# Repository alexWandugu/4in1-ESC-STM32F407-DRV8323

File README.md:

# 4-in-1 Quadcopter ESC (STM32F407 + DRV8323RS)

**High-performance 4-in-1 Electronic Speed Controller** for BLDC motors in quadcopters/drones.

## Specifications
- **Battery**: 4S LiPo (5.2Ah 35C/60C)
- **Motor**: 1400KV BLDC, ~7A max efficient current per motor
- **MOSFET**: MCG4D8N04YHE3-TP (x12 for 4-in-1)
- **Gate Driver**: DRV8323RS (x4)
- **MCU**: STM32F407VET6
- **Layout**: 4-in-1 ESC board
- **Firmware**: Custom (in development) — supports [target protocol, e.g., DShot, PWM]

## Features
- 4 independent 3-phase half-bridges
- High-current power stage optimized for 4S
- SPI / UART interface for configuration and telemetry
- Current sensing & protection

## Project Status
- Schematic V2 complete (multi-motor sheets)
- PCB layout in progress (see attached files)
- Firmware skeleton in development

## Repository Contents
- `project files (kicad)/` — KiCad 8+ schematic + PCB files
- `docs/` — Schematics PDF, BOM, images

## Quick Start
1. Clone repo
2. Open `hardware/ESC_4in1.kicad_pro` in KiCad
3. Review power stage, gate driver, and MCU sections
4. Generate Gerbers for manufacturing

## Firmware
(Instructions coming soon — STM32CubeIDE / PlatformIO)

## Contributing
Contributions welcome! See [CONTRIBUTING.md](CONTRIBUTING.md) (create later).

## License
MIT License — see [LICENSE](LICENSE) file.

---

## Roadmap & Future Improvements

### High Priority
- **Board Miniaturization**
  - Current dimensions: **108.6 × 77.5 mm** (4 layers)
  - Target: Reduce to **≤ 70 × 70 mm** or closer to standard 30.5×30.5mm / 40×40mm mounting patterns while maintaining proper thermal performance and clearance.
  - Optimize component placement and routing
  - Evaluate moving to 6-layer PCB if it enables significant size reduction
  - Improve power plane design and thermal vias under MOSFETs

- **Firmware Development**
  - Implement full BLDC FOC / Trapezoidal control using STM32F407
  - Support DShot600 / DShot1200 protocols
  - Current sensing and over-current protection
  - Telemetry (voltage, current, temperature, RPM)
  - DRV8323RS configuration via SPI
  - Sensorless startup and BEMF detection tuning
  - PID tuning for smooth throttle response

### Medium Priority
- Add onboard 5V / 3.3V BEC with better filtering
- Improve EMI/EMC performance (snubbers, capacitor placement)
- Add status LEDs and debugging interfaces (SWD + UART)
- Thermal simulation and real-world heat testing
- Input protection (TVS diodes, reverse polarity)
- Create a configurable GUI tool (Python / Qt) for tuning parameters

### Long Term
- Support higher current motors (optimize MOSFET cooling)
- 6S battery compatibility
- Open-source configurator tool
- Flight testing on a test quadcopter
- Documentation for assembly and calibration

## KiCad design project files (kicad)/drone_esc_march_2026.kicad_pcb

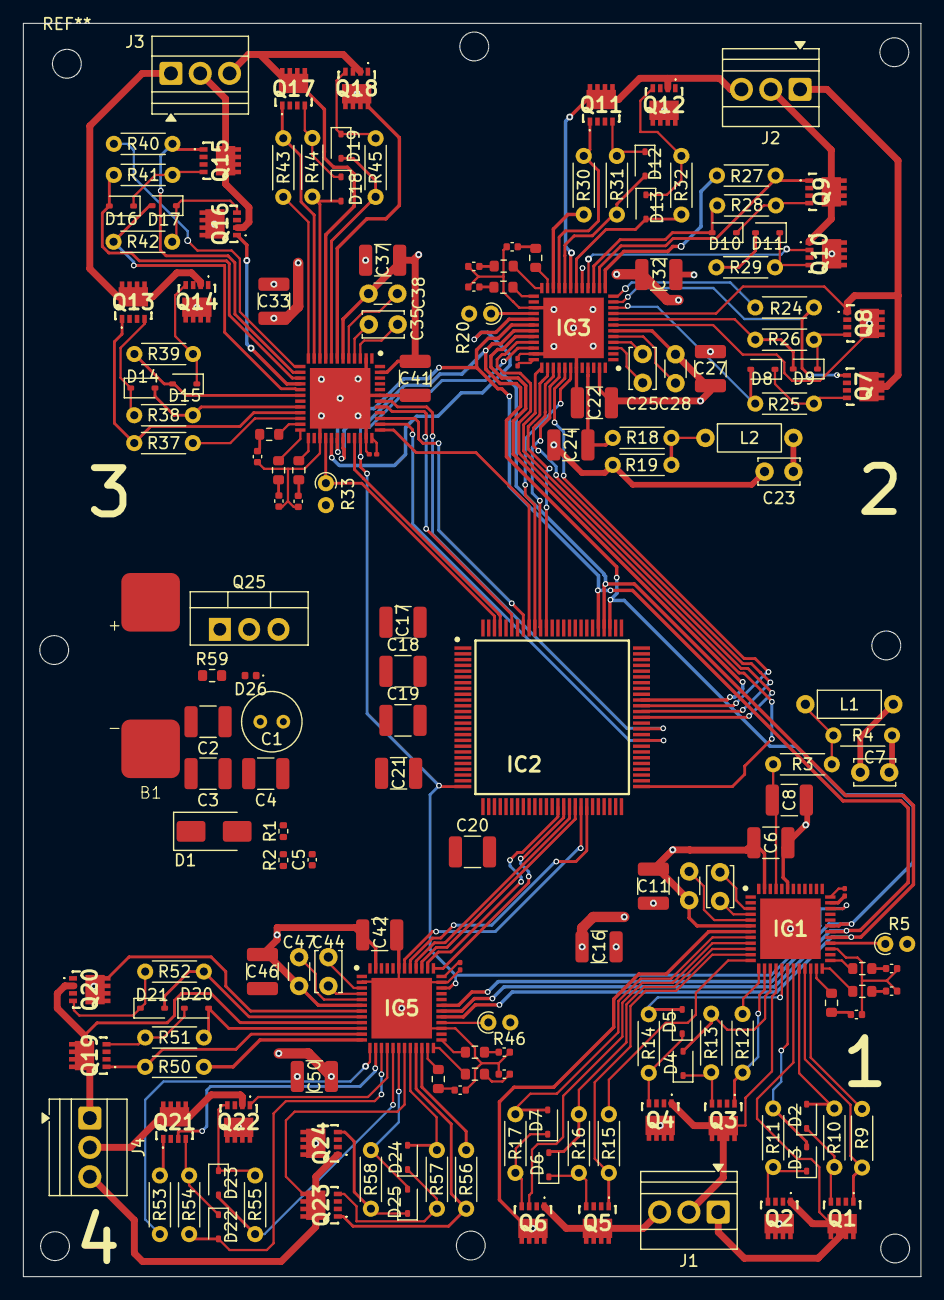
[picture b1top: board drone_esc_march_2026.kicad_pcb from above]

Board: 4 copper layers, 77.8 x 108.6 mm, 172 parts (0 on the bottom side), 162 nets.

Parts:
B1: Battery-Solder-Pads
C1: 1000u; C_Radial_D5.0mm_H7.0mm_P2.00mm
C2, C3, C4, C6, C22, C33, C42: 47u 25V; C_1210_3225Metric
C5, C13, C14, C15, C29, C30, C31, C36, C39, C40, C45, C48, C49: 100n; C_0402_1005Metric
C7, C23: 47u; C_Disc_D3.4mm_W2.1mm_P2.50mm
C8, C24: 22u 10V; C_1210_3225Metric
C9, C25, C35, C44: 100n 25V; C_Disc_D3.4mm_W2.1mm_P2.50mm
C10, C26, C34, C43: 0.1u; C_0201_0603Metric
C11, C27, C37, C46: 47u; C_1210_3225Metric
C12, C28, C38, C47: 2.2u; C_Disc_D3.0mm_W1.6mm_P2.50mm
C16, C32, C41, C50: 10u 25V; C_1210_3225Metric
C17, C18, C19, C20: 0.1u 10V; C_1210_3225Metric
C21: 4.7u 10V; C_1210_3225Metric
D1: SMAJ20CA; D_SMA
D2, D3, D4, D5, D6, D7, D8, D9, D10, D11, D12, D13, D14, D15, D16, D17, D18, D19, D20, D21, D22, D23, D24, D25: 1N4148WS; D_SOD-323
D26: D_Zener; D_0402_1005Metric
IC1, IC3, IC4, IC5: DRV8323RSRGZT; QFN50P700X700X100-49N-D
IC2: STM32F407VET6; QFP50P1600X1600X160-100N
J1, J2, J3, J4: Screw_Terminal_01x03; TerminalBlock_Xinya_XY308-2.54-3P_1x03_P2.54mm_Horizontal
L1, L2: 10u 1A; L_Axial_L5.3mm_D2.2mm_P7.62mm_Horizontal_Vishay_IM-1
Q1, Q2, Q3, Q4, Q5, Q6, Q7, Q8, Q9, Q10, Q11, Q12, Q13, Q14, Q15, Q16, Q17, Q18, Q19, Q20, Q21, Q22, Q23, Q24: MCG4D8N04YHE3-TP; MCG20N06HE3TP
Q25: IRF4905; TO-220-3_Vertical
R1: 10K; R_0402_1005Metric
R2: 1K; R_0402_1005Metric
R3, R18: 10K; R_Axial_DIN0204_L3.6mm_D1.6mm_P5.08mm_Horizontal
R4, R19: 3.3K; R_Axial_DIN0204_L3.6mm_D1.6mm_P5.08mm_Horizontal
R5, R20, R33, R46: 10K; R_Axial_DIN0204_L3.6mm_D1.6mm_P1.90mm_Vertical
R6, R7, R8, R21, R22, R23, R34, R35, R36, R47, R48, R49: 1K; R_0603_1608Metric
R9, R12, R15, R24, R27, R30, R37, R40, R43, R50, R53, R56: 5m; R_Axial_DIN0204_L3.6mm_D1.6mm_P5.08mm_Horizontal
R10, R11, R13, R14, R16, R17, R25, R26, R28, R29, R31, R32, R38, R39, R41, R42, R44, R45, R51, R52, R54, R55, R57, R58: 22; R_Axial_DIN0204_L3.6mm_D1.6mm_P5.08mm_Horizontal
R59: 10k; R_0603_1608Metric

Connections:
+3.3V: C7.1, C17.2, C18.2, C19.2, C20.2, C21.2, C23.1, IC2.11 (VDD_1), IC2.19 (VDD_2), IC2.22 (VDDA), IC2.28 (VDD_3), IC2.50 (VDD_4), IC2.75 (VDD_5), IC2.100 (VDD_6), L1.2, L2.2, R5.2, R20.2, R33.2, R46.2
+Vbat: C1.1, C2.1, C3.1, C4.1, C6.1, C11.2, C12.2, C16.1, C22.1, C27.2, C28.2, C32.1, C33.1, C37.2, C38.2, C41.1, C42.1, C46.2, C47.2, C50.1, D1.2 (A2), D26.1 (K), IC1.6 (VM), IC1.7 (VDRAIN), IC1.47 (VIN), IC3.6 (VM), IC3.7 (VDRAIN), IC3.47 (VIN), IC4.6 (VM), IC4.7 (VDRAIN), IC4.47 (VIN), IC5.6 (VM), IC5.7 (VDRAIN), IC5.47 (VIN), Q2.5 (D_1), Q2.6 (D_2), Q2.7 (D_3), Q2.8 (D_4), Q2.9 (D_5), Q4.5 (D_1), Q4.6 (D_2), Q4.7 (D_3), Q4.8 (D_4), Q4.9 (D_5), Q6.5 (D_1), Q6.6 (D_2), Q6.7 (D_3), Q6.8 (D_4), Q6.9 (D_5), Q8.5 (D_1), Q8.6 (D_2), Q8.7 (D_3), Q8.8 (D_4), Q8.9 (D_5), Q10.5 (D_1), Q10.6 (D_2), Q10.7 (D_3), Q10.8 (D_4), Q10.9 (D_5), Q12.5 (D_1), Q12.6 (D_2), Q12.7 (D_3), Q12.8 (D_4), Q12.9 (D_5), Q14.5 (D_1), Q14.6 (D_2), Q14.7 (D_3), Q14.8 (D_4), Q14.9 (D_5), Q16.5 (D_1), Q16.6 (D_2), Q16.7 (D_3), Q16.8 (D_4), Q16.9 (D_5), Q18.5 (D_1), Q18.6 (D_2), Q18.7 (D_3), Q18.8 (D_4), Q18.9 (D_5), Q20.5 (D_1), Q20.6 (D_2), Q20.7 (D_3), Q20.8 (D_4), Q20.9 (D_5), Q22.5 (D_1), Q22.6 (D_2), Q22.7 (D_3), Q22.8 (D_4), Q22.9 (D_5), Q24.5 (D_1), Q24.6 (D_2), Q24.7 (D_3), Q24.8 (D_4), Q24.9 (D_5), Q25.3 (S), R1.2
/GATE_DRIVER M2/CPH2: C25.2, IC3.4 (CPH)
/GATE_DRIVER M2/CPL2: C25.1, IC3.3 (CPL)
/GATE_DRIVER M2/DVDD2: C26.1, IC3.36 (DVDD)
/GATE_DRIVER M2/SOA2: IC3.25 (SOA), R21.1
/GATE_DRIVER M2/SOB2: IC3.24 (SOB), R22.1
/GATE_DRIVER M2/SOC2: IC3.23 (SOC), R23.1
/GATE_DRIVER M2/SW2: C24.2, IC3.45 (SW), R18.1
/GATE_DRIVER M2/VCP2: C28.1, IC3.5 (VCP)
/GATE_DRIVER M3/CPH3: C35.2, IC4.4 (CPH)
/GATE_DRIVER M3/CPL3: C35.1, IC4.3 (CPL)
/GATE_DRIVER M3/DVDD3: C34.1, IC4.36 (DVDD)
/GATE_DRIVER M3/SOA3: IC4.25 (SOA), R34.1
/GATE_DRIVER M3/SOB3: IC4.24 (SOB), R35.1
/GATE_DRIVER M3/SOC3: IC4.23 (SOC), R36.1
/GATE_DRIVER M3/VCP3: C38.1, IC4.5 (VCP)
/GATE_DRIVER M4/CPH4: C44.2, IC5.4 (CPH)
/GATE_DRIVER M4/CPL4: C44.1, IC5.3 (CPL)
/GATE_DRIVER M4/DVDD4: C43.1, IC5.36 (DVDD)
/GATE_DRIVER M4/SOA4: IC5.25 (SOA), R47.1
/GATE_DRIVER M4/SOB4: IC5.24 (SOB), R48.1
/GATE_DRIVER M4/SOC4: IC5.23 (SOC), R49.1
/GATE_DRIVER M4/VCP4: C47.1, IC5.5 (VCP)
/GATE_DRIVER_MAIN/CPH1: C9.2, IC1.4 (CPH)
/GATE_DRIVER_MAIN/CPL1: C9.1, IC1.3 (CPL)
/GATE_DRIVER_MAIN/DVDD1: C10.1, IC1.36 (DVDD)
/GATE_DRIVER_MAIN/SOA1: IC1.25 (SOA), R6.1
/GATE_DRIVER_MAIN/SOB1: IC1.24 (SOB), R7.1
/GATE_DRIVER_MAIN/SOC1: IC1.23 (SOC), R8.1
/GATE_DRIVER_MAIN/SW1: C8.2, IC1.45 (SW), R3.1
/GATE_DRIVER_MAIN/VCP1: C12.1, IC1.5 (VCP)
/POWER_BRIDGE M1/GHA1: D3.1 (K), Q2.4 (G), R11.2
/POWER_BRIDGE M1/GHB1: D5.1 (K), Q4.4 (G), R14.2
/POWER_BRIDGE M1/GHC1: D7.1 (K), Q6.4 (G), R17.2
/POWER_BRIDGE M1/GLA1: D2.1 (K), Q1.4 (G), R10.2
/POWER_BRIDGE M1/GLB1: D4.1 (K), Q3.4 (G), R13.2
/POWER_BRIDGE M1/GLC1: D6.1 (K), Q5.4 (G), R16.2
/POWER_BRIDGE M2/GHA2: D9.1 (K), Q8.4 (G), R26.2
/POWER_BRIDGE M2/GHB2: D11.1 (K), Q10.4 (G), R29.2
/POWER_BRIDGE M2/GHC2: D13.1 (K), Q12.4 (G), R32.2
/POWER_BRIDGE M2/GLA2: D8.1 (K), Q7.4 (G), R25.2
/POWER_BRIDGE M2/GLB2: D10.1 (K), Q9.4 (G), R28.2
/POWER_BRIDGE M2/GLC2: D12.1 (K), Q11.4 (G), R31.2
/POWER_BRIDGE M3/GHA3: D15.1 (K), Q14.4 (G), R39.2
/POWER_BRIDGE M3/GHB3: D17.1 (K), Q16.4 (G), R42.2
/POWER_BRIDGE M3/GHC3: D19.1 (K), Q18.4 (G), R45.2
/POWER_BRIDGE M3/GLA3: D14.1 (K), Q13.4 (G), R38.2
/POWER_BRIDGE M3/GLB3: D16.1 (K), Q15.4 (G), R41.2
/POWER_BRIDGE M3/GLC3: D18.1 (K), Q17.4 (G), R44.2
/POWER_BRIDGE M4/GHA4: D21.1 (K), Q20.4 (G), R52.2
/POWER_BRIDGE M4/GHB4: D23.1 (K), Q22.4 (G), R55.2
/POWER_BRIDGE M4/GHC4: D25.1 (K), Q24.4 (G), R58.2
/POWER_BRIDGE M4/GLA4: D20.1 (K), Q19.4 (G), R51.2
/POWER_BRIDGE M4/GLB4: D22.1 (K), Q21.4 (G), R54.2
/POWER_BRIDGE M4/GLC4: D24.1 (K), Q23.4 (G), R57.2
ADC123_A_M1: C13.2, IC2.15 (PC0), R6.2
ADC123_A_M2: C29.2, IC2.29 (PA4), R21.2
ADC123_A_M3: C36.2, IC2.33 (PC4), R34.2
ADC123_A_M4: C45.2, IC2.36 (PB1), R47.2
ADC123_B_M1: C14.2, IC2.16 (PC1), R7.2
ADC123_B_M2: C30.2, IC2.30 (PA5), R22.2
ADC123_B_M3: C39.2, IC2.34 (PC5), R35.2
ADC123_B_M4: C48.2, IC2.32 (PA7), R48.2
ADC123_C_M1: C15.2, IC2.17 (PC2), R8.2
ADC123_C_M2: C31.2, IC2.31 (PA6), R23.2
ADC123_C_M3: C40.2, IC2.35 (PB0), R36.2
ADC123_C_M4: C49.2, IC2.26 (PA3), R49.2
AMP_CALLIB: IC1.34 (CAL), IC2.25 (PA2), IC3.34 (CAL), IC4.34 (CAL), IC5.34 (CAL)
EN_DRIVER_M1: IC1.33 (ENABLE), IC2.24 (PA1)
EN_DRIVER_M2: IC2.51 (PB12), IC3.33 (ENABLE)
EN_DRIVER_M3: IC2.97 (PE0), IC4.33 (ENABLE)
EN_DRIVER_M4: IC2.2 (PE3), IC5.33 (ENABLE)
Fault_M1: IC1.28 (NFAULT), IC2.23 (PA0), R5.1
Fault_M2: IC2.37 (PB2), IC3.28 (NFAULT), R20.1
Fault_M3: IC2.98 (PE1), IC4.28 (NFAULT), R33.1
Fault_M4: IC2.3 (PE4), IC5.28 (NFAULT), R46.1
GHA_M1: D3.2 (A), IC1.18 (GHC), R11.1
GHA_M2: D9.2 (A), IC3.8 (GHA), R26.1
GHA_M3: D15.2 (A), IC4.18 (GHC), R39.1
GHA_M4: D21.2 (A), IC5.8 (GHA), R52.1
GHB_M1: D5.2 (A), IC1.17 (GHB), R14.1
GHB_M2: D11.2 (A), IC3.17 (GHB), R29.1
GHB_M3: D17.2 (A), IC4.17 (GHB), R42.1
GHB_M4: D23.2 (A), IC5.17 (GHB), R55.1
GHC_M1: D7.2 (A), IC1.8 (GHA), R17.1
GHC_M2: D13.2 (A), IC3.18 (GHC), R32.1
GHC_M3: D19.2 (A), IC4.8 (GHA), R45.1
GHC_M4: D25.2 (A), IC5.18 (GHC), R58.1
GLA_M1: D2.2 (A), IC1.20 (GLC), R10.1
GLA_M2: D8.2 (A), IC3.10 (GLA), R25.1
GLA_M3: D14.2 (A), IC4.20 (GLC), R38.1
GLA_M4: D20.2 (A), IC5.10 (GLA), R51.1
GLB_M1: D4.2 (A), IC1.15 (GLB), R13.1
GLB_M2: D10.2 (A), IC3.15 (GLB), R28.1
GLB_M3: D16.2 (A), IC4.15 (GLB), R41.1
GLB_M4: D22.2 (A), IC5.15 (GLB), R54.1
GLC_M1: D6.2 (A), IC1.10 (GLA), R16.1
GLC_M2: D12.2 (A), IC3.20 (GLC), R31.1
GLC_M3: D18.2 (A), IC4.10 (GLA), R44.1
GLC_M4: D24.2 (A), IC5.20 (GLC), R57.1
GND: B1.2 (-), C1.2, C2.2, C3.2, C4.2, C5.1, C6.2, C7.2, C8.1, C10.2, C11.1, C13.1, C14.1, C15.1, C16.2, C17.1, C18.1, C19.1, C20.1, C21.1, C22.2, C23.2, C24.1, C26.2, C27.1, C29.1, C30.1, C31.1, C32.2, C33.2, C34.2, C36.1, C37.1, C39.1, C40.1, C41.2, C42.2, C43.2, C45.1, C46.1, C48.1, C49.1, C50.2, D1.1 (A1), IC1.2 (PGND), IC1.12 (SNA), IC1.13 (SNB), IC1.22 (SNC), IC1.27 (DGND), IC1.35 (AGND), IC1.43 (BGND), IC1.49 (THERMAL_PAD), IC2.10 (VSS_1), IC2.20 (VSSA), IC2.27 (VSS_2), IC2.74 (VSS_3), IC2.99 (VSS_4), IC3.2 (PGND), IC3.12 (SNA), IC3.13 (SNB), IC3.22 (SNC), IC3.27 (DGND), IC3.35 (AGND), IC3.43 (BGND), IC3.49 (THERMAL_PAD), IC4.2 (PGND), IC4.12 (SNA), IC4.13 (SNB), IC4.22 (SNC), IC4.27 (DGND), IC4.35 (AGND), IC4.43 (BGND), IC4.49 (THERMAL_PAD), IC5.2 (PGND), IC5.12 (SNA), IC5.13 (SNB), IC5.22 (SNC), IC5.27 (DGND), IC5.35 (AGND), IC5.43 (BGND), IC5.49 (THERMAL_PAD), R2.1, R4.1, R9.1, R12.1, R15.1, R19.1, R24.1, R27.1, R30.1, R37.1, R40.1, R43.1, R50.1, R53.1, R56.1, R59.1
LSA ShuntAmp_M1+: IC1.21 (SPC), Q1.1 (S_1), Q1.2 (S_2), Q1.3 (S_3), R9.2
LSA ShuntAmp_M2+: IC3.11 (SPA), Q7.1 (S_1), Q7.2 (S_2), Q7.3 (S_3), R24.2
LSA ShuntAmp_M3+: IC4.21 (SPC), Q13.1 (S_1), Q13.2 (S_2), Q13.3 (S_3), R37.2
LSA ShuntAmp_M4+: IC5.11 (SPA), Q19.1 (S_1), Q19.2 (S_2), Q19.3 (S_3), R50.2
LSB ShuntAmp_M1+: IC1.14 (SPB), Q3.1 (S_1), Q3.2 (S_2), Q3.3 (S_3), R12.2
LSB ShuntAmp_M2+: IC3.14 (SPB), Q9.1 (S_1), Q9.2 (S_2), Q9.3 (S_3), R27.2
LSB ShuntAmp_M3+: IC4.14 (SPB), Q15.1 (S_1), Q15.2 (S_2), Q15.3 (S_3), R40.2
LSB ShuntAmp_M4+: IC5.14 (SPB), Q21.1 (S_1), Q21.2 (S_2), Q21.3 (S_3), R53.2
LSC ShuntAmp_M1+: IC1.11 (SPA), Q5.1 (S_1), Q5.2 (S_2), Q5.3 (S_3), R15.2
LSC ShuntAmp_M2+: IC3.21 (SPC), Q11.1 (S_1), Q11.2 (S_2), Q11.3 (S_3), R30.2
LSC ShuntAmp_M3+: IC4.11 (SPA), Q17.1 (S_1), Q17.2 (S_2), Q17.3 (S_3), R43.2
LSC ShuntAmp_M4+: IC5.21 (SPC), Q23.1 (S_1), Q23.2 (S_2), Q23.3 (S_3), R56.2
unnamed: B1.1 (+), Q25.2 (D)
unnamed: D26.2 (A), Q25.1 (G), R59.2
unnamed: L1.1, R3.2, R4.2
unnamed: L2.1, R18.2, R19.2
PHASE A - M1: IC1.19 (SHC), J1.1, Q1.5 (D_1), Q1.6 (D_2), Q1.7 (D_3), Q1.8 (D_4), Q1.9 (D_5), Q2.1 (S_1), Q2.2 (S_2), Q2.3 (S_3)
PHASE A - M2: IC3.9 (SHA), J2.1, Q7.5 (D_1), Q7.6 (D_2), Q7.7 (D_3), Q7.8 (D_4), Q7.9 (D_5), Q8.1 (S_1), Q8.2 (S_2), Q8.3 (S_3)
PHASE A - M3: IC4.19 (SHC), J3.1, Q13.5 (D_1), Q13.6 (D_2), Q13.7 (D_3), Q13.8 (D_4), Q13.9 (D_5), Q14.1 (S_1), Q14.2 (S_2), Q14.3 (S_3)
PHASE A - M4: IC5.9 (SHA), J4.1, Q19.5 (D_1), Q19.6 (D_2), Q19.7 (D_3), Q19.8 (D_4), Q19.9 (D_5), Q20.1 (S_1), Q20.2 (S_2), Q20.3 (S_3)
PHASE B - M1: IC1.16 (SHB), J1.2, Q3.5 (D_1), Q3.6 (D_2), Q3.7 (D_3), Q3.8 (D_4), Q3.9 (D_5), Q4.1 (S_1), Q4.2 (S_2), Q4.3 (S_3)
PHASE B - M2: IC3.16 (SHB), J2.2, Q9.5 (D_1), Q9.6 (D_2), Q9.7 (D_3), Q9.8 (D_4), Q9.9 (D_5), Q10.1 (S_1), Q10.2 (S_2), Q10.3 (S_3)
PHASE B - M3: IC4.16 (SHB), J3.2, Q15.5 (D_1), Q15.6 (D_2), Q15.7 (D_3), Q15.8 (D_4), Q15.9 (D_5), Q16.1 (S_1), Q16.2 (S_2), Q16.3 (S_3)
PHASE B - M4: IC5.16 (SHB), J4.2, Q21.5 (D_1), Q21.6 (D_2), Q21.7 (D_3), Q21.8 (D_4), Q21.9 (D_5), Q22.1 (S_1), Q22.2 (S_2), Q22.3 (S_3)
PHASE C - M1: IC1.9 (SHA), J1.3, Q5.5 (D_1), Q5.6 (D_2), Q5.7 (D_3), Q5.8 (D_4), Q5.9 (D_5), Q6.1 (S_1), Q6.2 (S_2), Q6.3 (S_3)
PHASE C - M2: IC3.19 (SHC), J2.3, Q11.5 (D_1), Q11.6 (D_2), Q11.7 (D_3), Q11.8 (D_4), Q11.9 (D_5), Q12.1 (S_1), Q12.2 (S_2), Q12.3 (S_3)
PHASE C - M3: IC4.9 (SHA), J3.3, Q17.5 (D_1), Q17.6 (D_2), Q17.7 (D_3), Q17.8 (D_4), Q17.9 (D_5), Q18.1 (S_1), Q18.2 (S_2), Q18.3 (S_3)
PHASE C - M4: IC5.19 (SHC), J4.3, Q23.5 (D_1), Q23.6 (D_2), Q23.7 (D_3), Q23.8 (D_4), Q23.9 (D_5), Q24.1 (S_1), Q24.2 (S_2), Q24.3 (S_3)
SPI1_MISO: IC1.29 (SDO), IC2.79 (PC11), IC3.29 (SDO), IC4.29 (SDO), IC5.29 (SDO)
SPI1_MOSI: IC1.30 (SDI), IC2.80 (PC12), IC3.30 (SDI), IC4.30 (SDI), IC5.30 (SDI)
SPI1_NSS_M1: IC1.32 (NSCS), IC2.83 (PD2)
SPI1_NSS_M2: IC2.66 (PC9), IC3.32 (NSCS)
SPI1_NSS_M3: IC2.62 (PD15), IC4.32 (NSCS)
SPI1_NSS_M4: IC2.1 (PE2), IC5.32 (NSCS)
SPI1_SCK: IC1.31 (SCLK), IC2.78 (PC10), IC3.31 (SCLK), IC4.31 (SCLK), IC5.31 (SCLK)
VbatSense: C5.2, IC2.18 (PC3), R1.1, R2.2
hsideA_M1: IC1.37 (INHA), IC2.67 (PA8)
hsideA_M2: IC2.63 (PC6), IC3.37 (INHA)
hsideA_M3: IC2.92 (PB6), IC4.37 (INHA)
hsideA_M4: IC2.40 (PE9), IC5.37 (INHA)
hsideB_M1: IC1.39 (INHB), IC2.68 (PA9)
hsideB_M2: IC2.64 (PC7), IC3.39 (INHB)
hsideB_M3: IC2.93 (PB7), IC4.39 (INHB)
hsideB_M4: IC2.42 (PE11), IC5.39 (INHB)
hsideC_M1: IC1.41 (INHC), IC2.69 (PA10)
hsideC_M2: IC2.65 (PC8), IC3.41 (INHC)
hsideC_M3: IC2.95 (PB8), IC4.41 (INHC)
hsideC_M4: IC2.44 (PE13), IC5.41 (INHC)
lsideA_M1: IC1.38 (INLA), IC2.52 (PB13)
lsideA_M2: IC2.89 (PB3), IC3.38 (INLA)
lsideA_M3: IC2.59 (PD12), IC4.38 (INLA)
lsideA_M4: IC2.39 (PE8), IC5.38 (INLA)
lsideB_M1: IC1.40 (INLB), IC2.53 (PB14)
lsideB_M2: IC2.90 (PB4), IC3.40 (INLB)
lsideB_M3: IC2.60 (PD13), IC4.40 (INLB)
lsideB_M4: IC2.41 (PE10), IC5.40 (INLB)
lsideC_M1: IC1.42 (INLC), IC2.54 (PB15)
lsideC_M2: IC2.91 (PB5), IC3.42 (INLC)
lsideC_M3: IC2.61 (PD14), IC4.42 (INLC)
lsideC_M4: IC2.43 (PE12), IC5.42 (INLC)

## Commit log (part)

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2026-05-09 Uploaded docs
    Progress documentation as of May 8, 2026
2026-05-09 Kicad Project Files Upload
    Kicad 10 project files and custom footprint libraries as of May 8, 2026
2026-05-09 Rename PCB 3D top view 8-05-2026.png to PCB-3D-top-view-8_05_2026.png
2026-05-09 Revert "Rename PCB 3D top view 8-05-2026.png to PCB-3D-top-view-8_05_2026.png"
    This reverts commit 9f7adb26eb5f19115e6abef4567a2fc4bce30dc8.
2026-05-09 Replaced and Renamed Images
    Replaced images with images whose naming follows recommended practices to enable robust relative paths in the READme
2026-05-09 Create gate_drivers_schematic_8-05-2026.png
    Screenshot of motor 1's gate drivers schematic page
2026-05-09 Revise README for 4-in-1 Quadcopter ESC
    Expanded README with detailed specifications, features, project status, and quick start instructions.
2026-05-09 Add roadmap and future improvements section to README
    Added a roadmap section outlining future improvements and priorities for the project, including high, medium, and long-term goals.
